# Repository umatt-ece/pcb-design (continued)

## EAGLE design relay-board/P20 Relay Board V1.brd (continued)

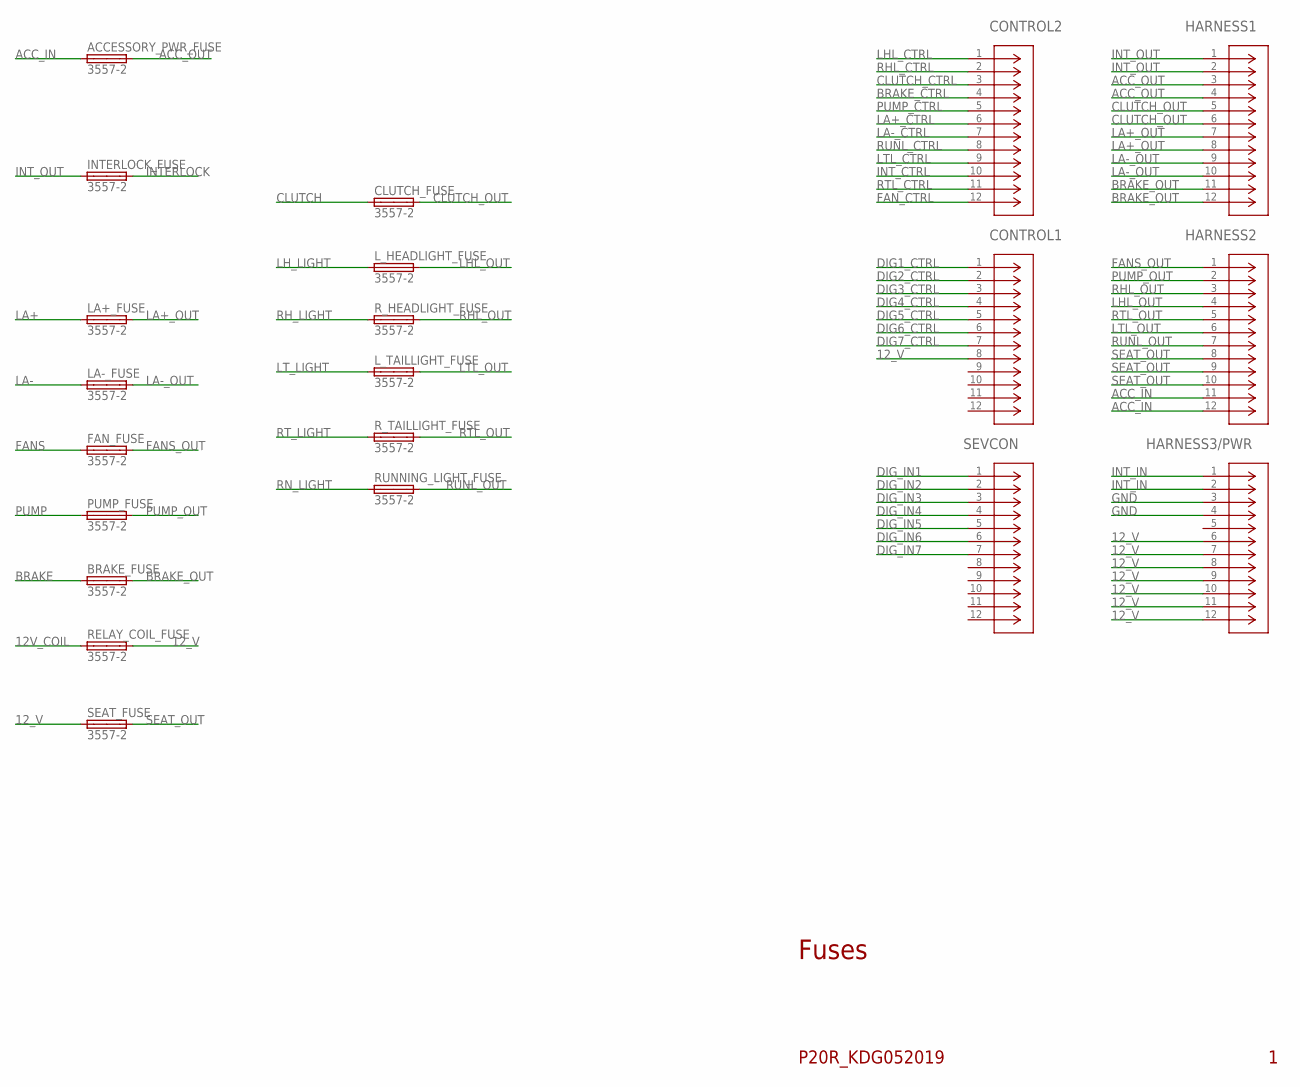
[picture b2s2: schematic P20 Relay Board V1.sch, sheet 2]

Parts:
ACCESSORY_PWR_FUSE: 3557-2; FUSE_3557-2
BRAKE_FUSE: 3557-2; FUSE_3557-2
CLUTCH_FUSE: 3557-2; FUSE_3557-2
CONTROL1, CONTROL2: DTM13-12PA; CONN12_DTM13-12PA
FAN_FUSE: 3557-2; FUSE_3557-2
HARNESS1, HARNESS2, HARNESS3/PWR: DTM13-12PA; CONN12_DTM13-12PA
INTERLOCK_FUSE: 3557-2; FUSE_3557-2
LA+_FUSE: 3557-2; FUSE_3557-2
LA-_FUSE: 3557-2; FUSE_3557-2
L_HEADLIGHT_FUSE: 3557-2; FUSE_3557-2
L_TAILLIGHT_FUSE: 3557-2; FUSE_3557-2
PUMP_FUSE: 3557-2; FUSE_3557-2
RELAY_COIL_FUSE: 3557-2; FUSE_3557-2
RUNNING_LIGHT_FUSE: 3557-2; FUSE_3557-2
R_HEADLIGHT_FUSE: 3557-2; FUSE_3557-2
R_TAILLIGHT_FUSE: 3557-2; FUSE_3557-2
SEAT_FUSE: 3557-2; FUSE_3557-2
SEVCON: DTM13-12PA; CONN12_DTM13-12PA

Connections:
12V_COIL: RELAY_COIL_FUSE.1 (1A); also elsewhere on the board
12_V: CONTROL1.8, HARNESS3/PWR.6, HARNESS3/PWR.7, HARNESS3/PWR.8, HARNESS3/PWR.9, HARNESS3/PWR.10, HARNESS3/PWR.11, HARNESS3/PWR.12, RELAY_COIL_FUSE.3 (2A), SEAT_FUSE.1 (1A); also elsewhere on the board
ACC_IN: ACCESSORY_PWR_FUSE.1 (1A), HARNESS2.11, HARNESS2.12
ACC_OUT: ACCESSORY_PWR_FUSE.3 (2A), HARNESS1.3, HARNESS1.4
BRAKE: BRAKE_FUSE.1 (1A); also elsewhere on the board
BRAKE_CTRL: CONTROL2.4; also elsewhere on the board
BRAKE_OUT: BRAKE_FUSE.3 (2A), HARNESS1.11, HARNESS1.12
CLUTCH: CLUTCH_FUSE.1 (1A); also elsewhere on the board
CLUTCH_CTRL: CONTROL2.3; also elsewhere on the board
CLUTCH_OUT: CLUTCH_FUSE.3 (2A), HARNESS1.5, HARNESS1.6
DIG1_CTRL: CONTROL1.1; also elsewhere on the board
DIG2_CTRL: CONTROL1.2; also elsewhere on the board
DIG3_CTRL: CONTROL1.3; also elsewhere on the board
DIG4_CTRL: CONTROL1.4; also elsewhere on the board
DIG5_CTRL: CONTROL1.5; also elsewhere on the board
DIG6_CTRL: CONTROL1.6; also elsewhere on the board
DIG7_CTRL: CONTROL1.7; also elsewhere on the board
DIG_IN1: SEVCON.1; also elsewhere on the board
DIG_IN2: SEVCON.2; also elsewhere on the board
DIG_IN3: SEVCON.3; also elsewhere on the board
DIG_IN4: SEVCON.4; also elsewhere on the board
DIG_IN5: SEVCON.5; also elsewhere on the board
DIG_IN6: SEVCON.6; also elsewhere on the board
DIG_IN7: SEVCON.7; also elsewhere on the board
FANS: FAN_FUSE.1 (1A); also elsewhere on the board
FANS_OUT: FAN_FUSE.3 (2A), HARNESS2.1
FAN_CTRL: CONTROL2.12; also elsewhere on the board
GND: HARNESS3/PWR.3, HARNESS3/PWR.4; also elsewhere on the board
INTERLOCK: INTERLOCK_FUSE.3 (2A); also elsewhere on the board
INT_CTRL: CONTROL2.10; also elsewhere on the board
INT_IN: HARNESS3/PWR.1, HARNESS3/PWR.2; also elsewhere on the board
INT_OUT: HARNESS1.1, HARNESS1.2, INTERLOCK_FUSE.1 (1A)
LA+: LA+_FUSE.1 (1A); also elsewhere on the board
LA+_CTRL: CONTROL2.6; also elsewhere on the board
LA+_OUT: HARNESS1.7, HARNESS1.8, LA+_FUSE.3 (2A)
LA-: LA-_FUSE.1 (1A); also elsewhere on the board
LA-_CTRL: CONTROL2.7; also elsewhere on the board
LA-_OUT: HARNESS1.9, HARNESS1.10, LA-_FUSE.3 (2A)
LHL_CTRL: CONTROL2.1; also elsewhere on the board
LHL_OUT: HARNESS2.4, L_HEADLIGHT_FUSE.3 (2A)
LH_LIGHT: L_HEADLIGHT_FUSE.1 (1A); also elsewhere on the board
LTL_CTRL: CONTROL2.9; also elsewhere on the board
LTL_OUT: HARNESS2.6, L_TAILLIGHT_FUSE.3 (2A)
LT_LIGHT: L_TAILLIGHT_FUSE.1 (1A); also elsewhere on the board
PUMP: PUMP_FUSE.1 (1A); also elsewhere on the board
PUMP_CTRL: CONTROL2.5; also elsewhere on the board
PUMP_OUT: HARNESS2.2, PUMP_FUSE.3 (2A)
RHL_CTRL: CONTROL2.2; also elsewhere on the board
RHL_OUT: HARNESS2.3, R_HEADLIGHT_FUSE.3 (2A)
RH_LIGHT: R_HEADLIGHT_FUSE.1 (1A); also elsewhere on the board
RN_LIGHT: RUNNING_LIGHT_FUSE.1 (1A); also elsewhere on the board
RTL_CTRL: CONTROL2.11; also elsewhere on the board
RTL_OUT: HARNESS2.5, R_TAILLIGHT_FUSE.3 (2A)
RT_LIGHT: R_TAILLIGHT_FUSE.1 (1A); also elsewhere on the board
RUNL_CTRL: CONTROL2.8; also elsewhere on the board
RUNL_OUT: HARNESS2.7, RUNNING_LIGHT_FUSE.3 (2A)
SEAT_OUT: HARNESS2.8, HARNESS2.9, HARNESS2.10, SEAT_FUSE.3 (2A)

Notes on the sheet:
Fuses
P20R_KDG052019

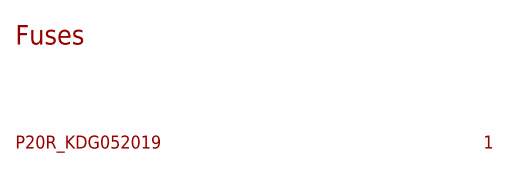
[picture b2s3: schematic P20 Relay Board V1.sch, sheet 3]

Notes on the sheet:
Fuses
P20R_KDG052019

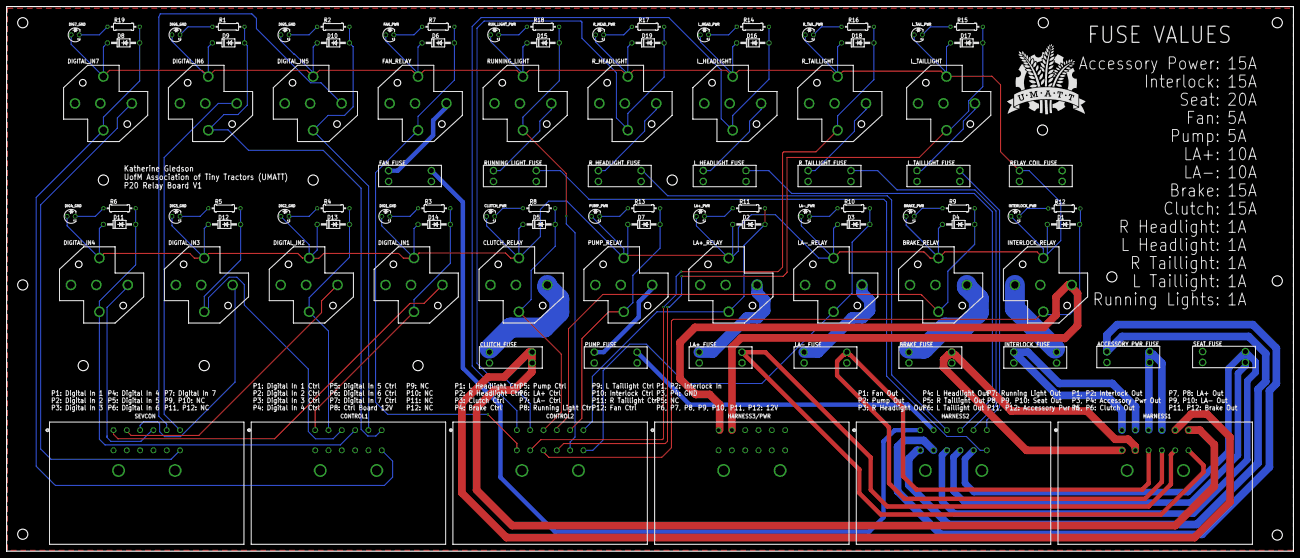
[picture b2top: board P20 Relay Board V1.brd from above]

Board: 2 copper layers, 405.1 x 171.4 mm, 97 parts (0 on the bottom side), 76 nets.

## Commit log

2024-01-22 added legacy schematics to the repository
2024-05-18 legacy schematics
